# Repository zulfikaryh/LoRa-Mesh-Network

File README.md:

# LoRa-Mesh-Network

Source code is developed using the RadioHead library because it includes an implementation of mesh networking. For details on how the mesh works, see the RadioHead documentation about it.

Each node has an identity which is stored in the device EEPROM.

Each node attempts to communicate with every other node in the network, and in the process it keeps track of a routing table that describes which nodes it can talk to directly and which nodes that messages get routed through when there is no direct connection available. It also keeps track of the signal strength that it “hears” from a node when it communicates with it directly

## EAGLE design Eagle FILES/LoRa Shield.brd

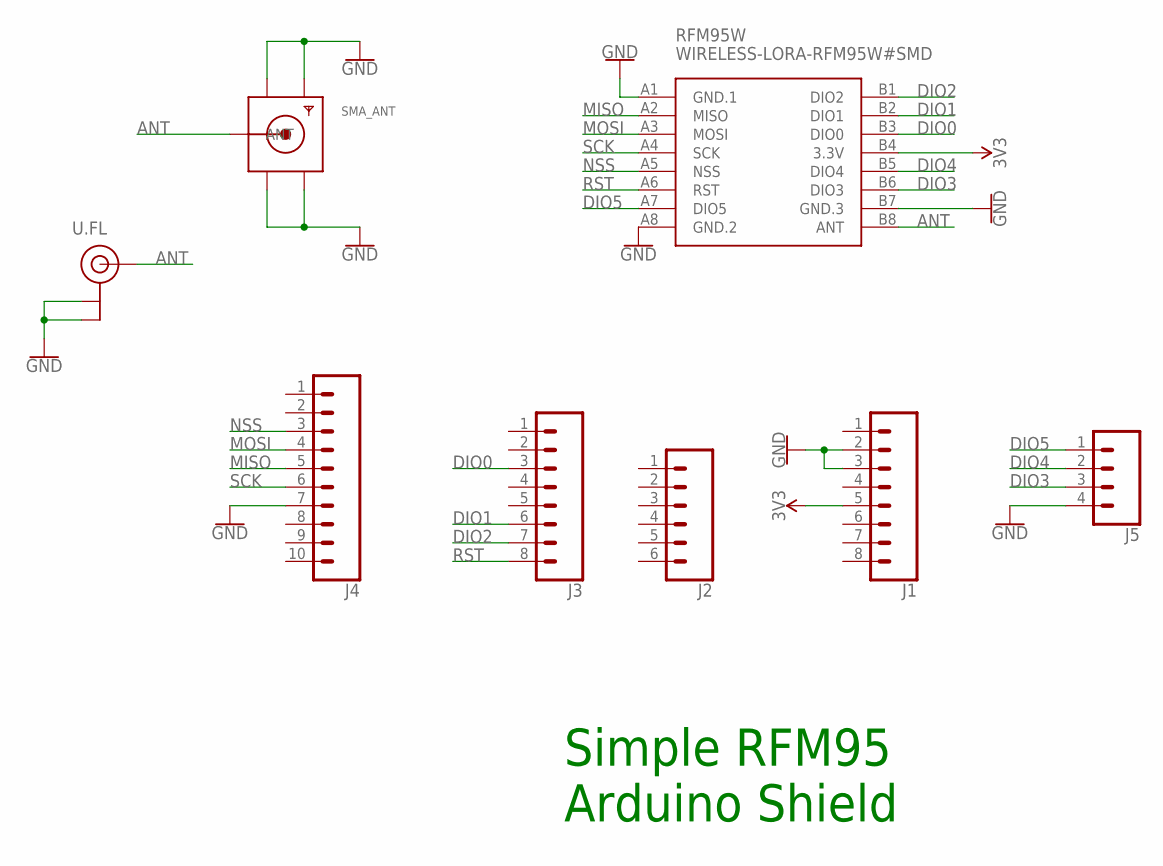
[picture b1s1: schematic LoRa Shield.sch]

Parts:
J1, J3: CONN_08"; 1X08
J2: CONN_06SILK_FEMALE_PTH; 1X06
J4: CONN_10"; 1X10
J5: CONN_04PTH; 1X04
RFM95W: WIRELESS-LORA-RFM95W#SMD
SMA_ANT: SMACONNECTOR; SMA90_DIP
U.FL: U.FL

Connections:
ANT: RFM95W.B8 (ANT), SMA_ANT.ANTENNA (ANT), U.FL.FEED (SIGNAL)
DIO0: J3.3, RFM95W.B3 (DIO0)
DIO1: J3.6, RFM95W.B2 (DIO1)
DIO2: J3.7, RFM95W.B1 (DIO2)
DIO3: J5.3, RFM95W.B6 (DIO3)
DIO4: J5.2, RFM95W.B5 (DIO4)
DIO5: J5.1, RFM95W.A7 (DIO5)
GND: J1.2, J1.3, J4.7, J5.4, RFM95W.A1 (GND.1), RFM95W.A8 (GND.2), RFM95W.B7 (GND.3), SMA_ANT.GND1, SMA_ANT.GND2, SMA_ANT.GND3, SMA_ANT.GND4, U.FL.1 (GND), U.FL.2 (GND)
MISO: J4.5, RFM95W.A2 (MISO)
MOSI: J4.4, RFM95W.A3 (MOSI)
NSS: J4.3, RFM95W.A5 (NSS)
RST: J3.8, RFM95W.A6 (RST)
SCK: J4.6, RFM95W.A4 (SCK)
VCC: J1.5, RFM95W.B4 (3.3V)

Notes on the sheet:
Simple RFM95 Arduino Shield

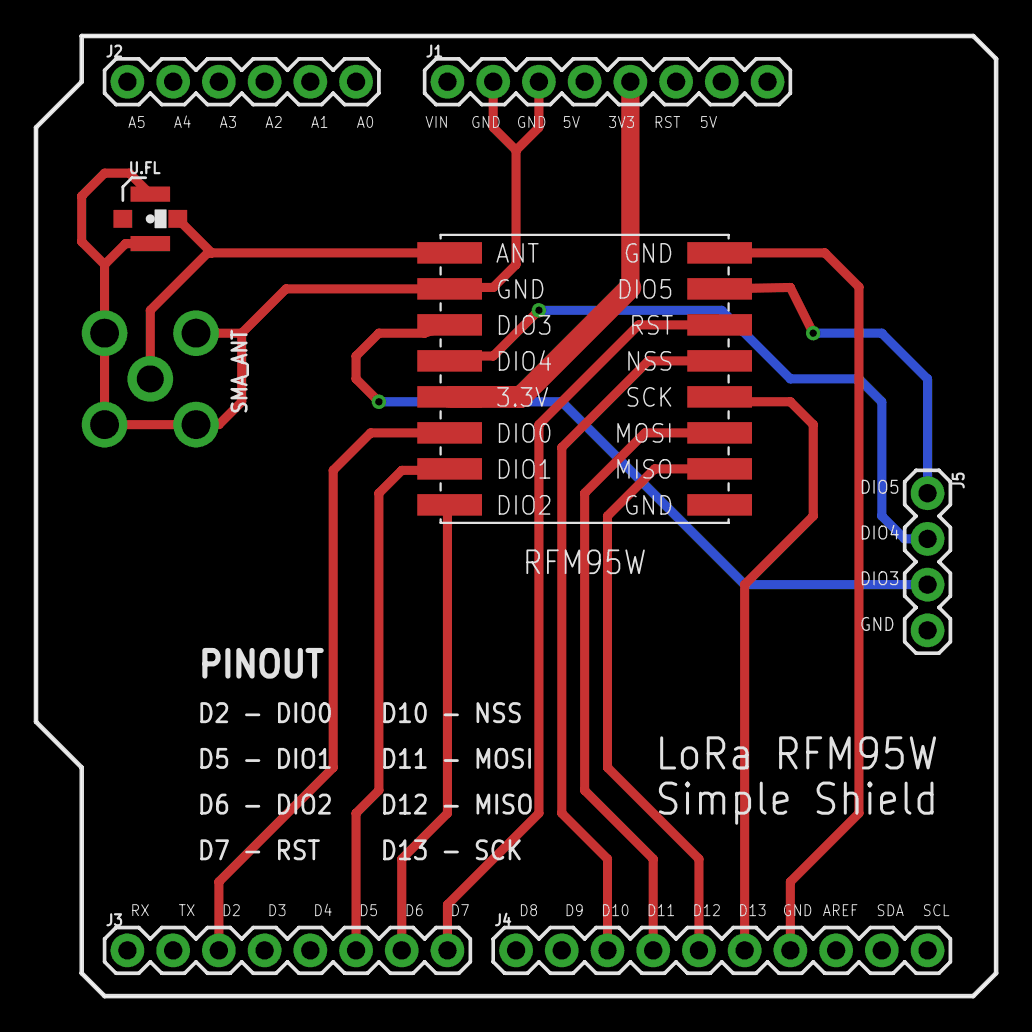
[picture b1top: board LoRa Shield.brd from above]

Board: 2 copper layers, 53.3 x 53.3 mm, 8 parts (0 on the bottom side), 14 nets.

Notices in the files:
parts and their libraries:
diy-modules: Released under the Creative Commons Attribution 4.0 International License: http://creativecommons.org/licenses/by/4.0
SparkFun-Connectors: Licensing: Creative Commons ShareAlike 4.0 International - https://creativecommons.org/licenses/by-sa/4.0
